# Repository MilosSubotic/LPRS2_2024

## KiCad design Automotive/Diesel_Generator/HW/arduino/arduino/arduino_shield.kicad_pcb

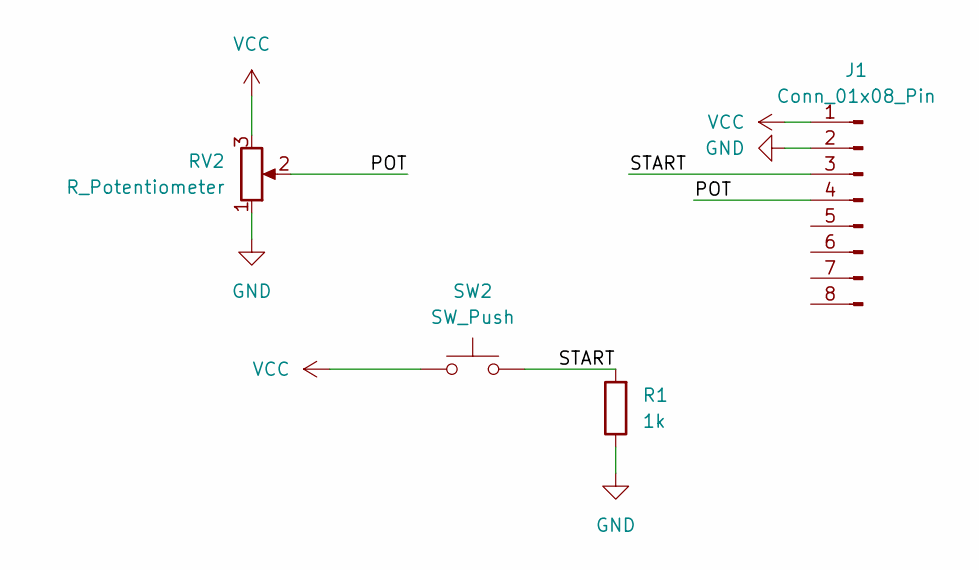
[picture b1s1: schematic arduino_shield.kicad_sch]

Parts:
J1: Conn_01x08_Pin; PinHeader_1x08_P2.54mm_Horizontal
R1: 1k; R_Axial_DIN0207_L6.3mm_D2.5mm_Pinf_Horizontal
RV2: R_Potentiometer; TerminalBlock_Phoenix_MKDS-3-3-5.08_1x03_P5.08mm_Horizontal
SW2: SW_Push; SW_PUSH_Color_B9mm_D12mm_P5.08mm

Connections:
/POT: J1.4, RV2.2
/START: J1.3, R1.2, SW2.2
GND: J1.2, R1.1, RV2.1
VCC: J1.1, RV2.3, SW2.1

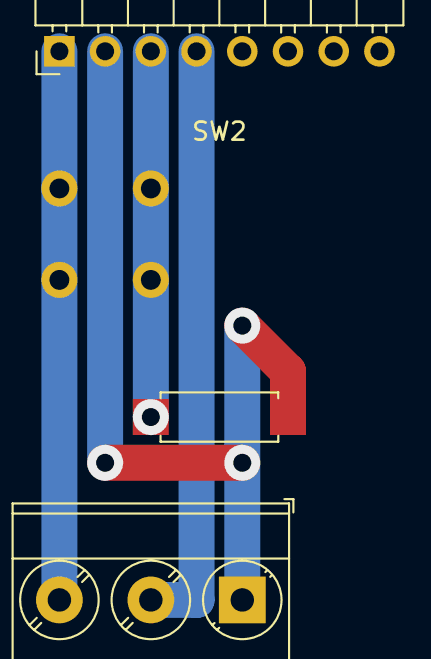
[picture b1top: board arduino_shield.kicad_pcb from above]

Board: 2 copper layers, 4 parts (0 on the bottom side), 4 nets.

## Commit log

2024-05-28 Implemented stepper routine
2024-05-28 renamed stepper.ino
2024-05-30 Movement on both steppers, added defines
2024-06-17 Added schema for control box and generator
2024-06-20 Button solenoid control
2024-06-21 Added schemas
2024-06-21 Docs added
2024-06-21 Rename LPRS2.pdf to Documentation.pdf
2024-06-21 Docs added + latex file
2024-06-21 Changed tex
2024-06-22 TODO.
2024-07-05 Merging.
2024-07-05 Trash.
2024-07-05 Merge.
2024-07-05 What to install.
2024-07-08 Rename.
2024-07-08 Path.
2024-07-08 Ignore
2024-07-09 Correct names.
2024-07-09 Clean.
2024-07-09 Doc.
